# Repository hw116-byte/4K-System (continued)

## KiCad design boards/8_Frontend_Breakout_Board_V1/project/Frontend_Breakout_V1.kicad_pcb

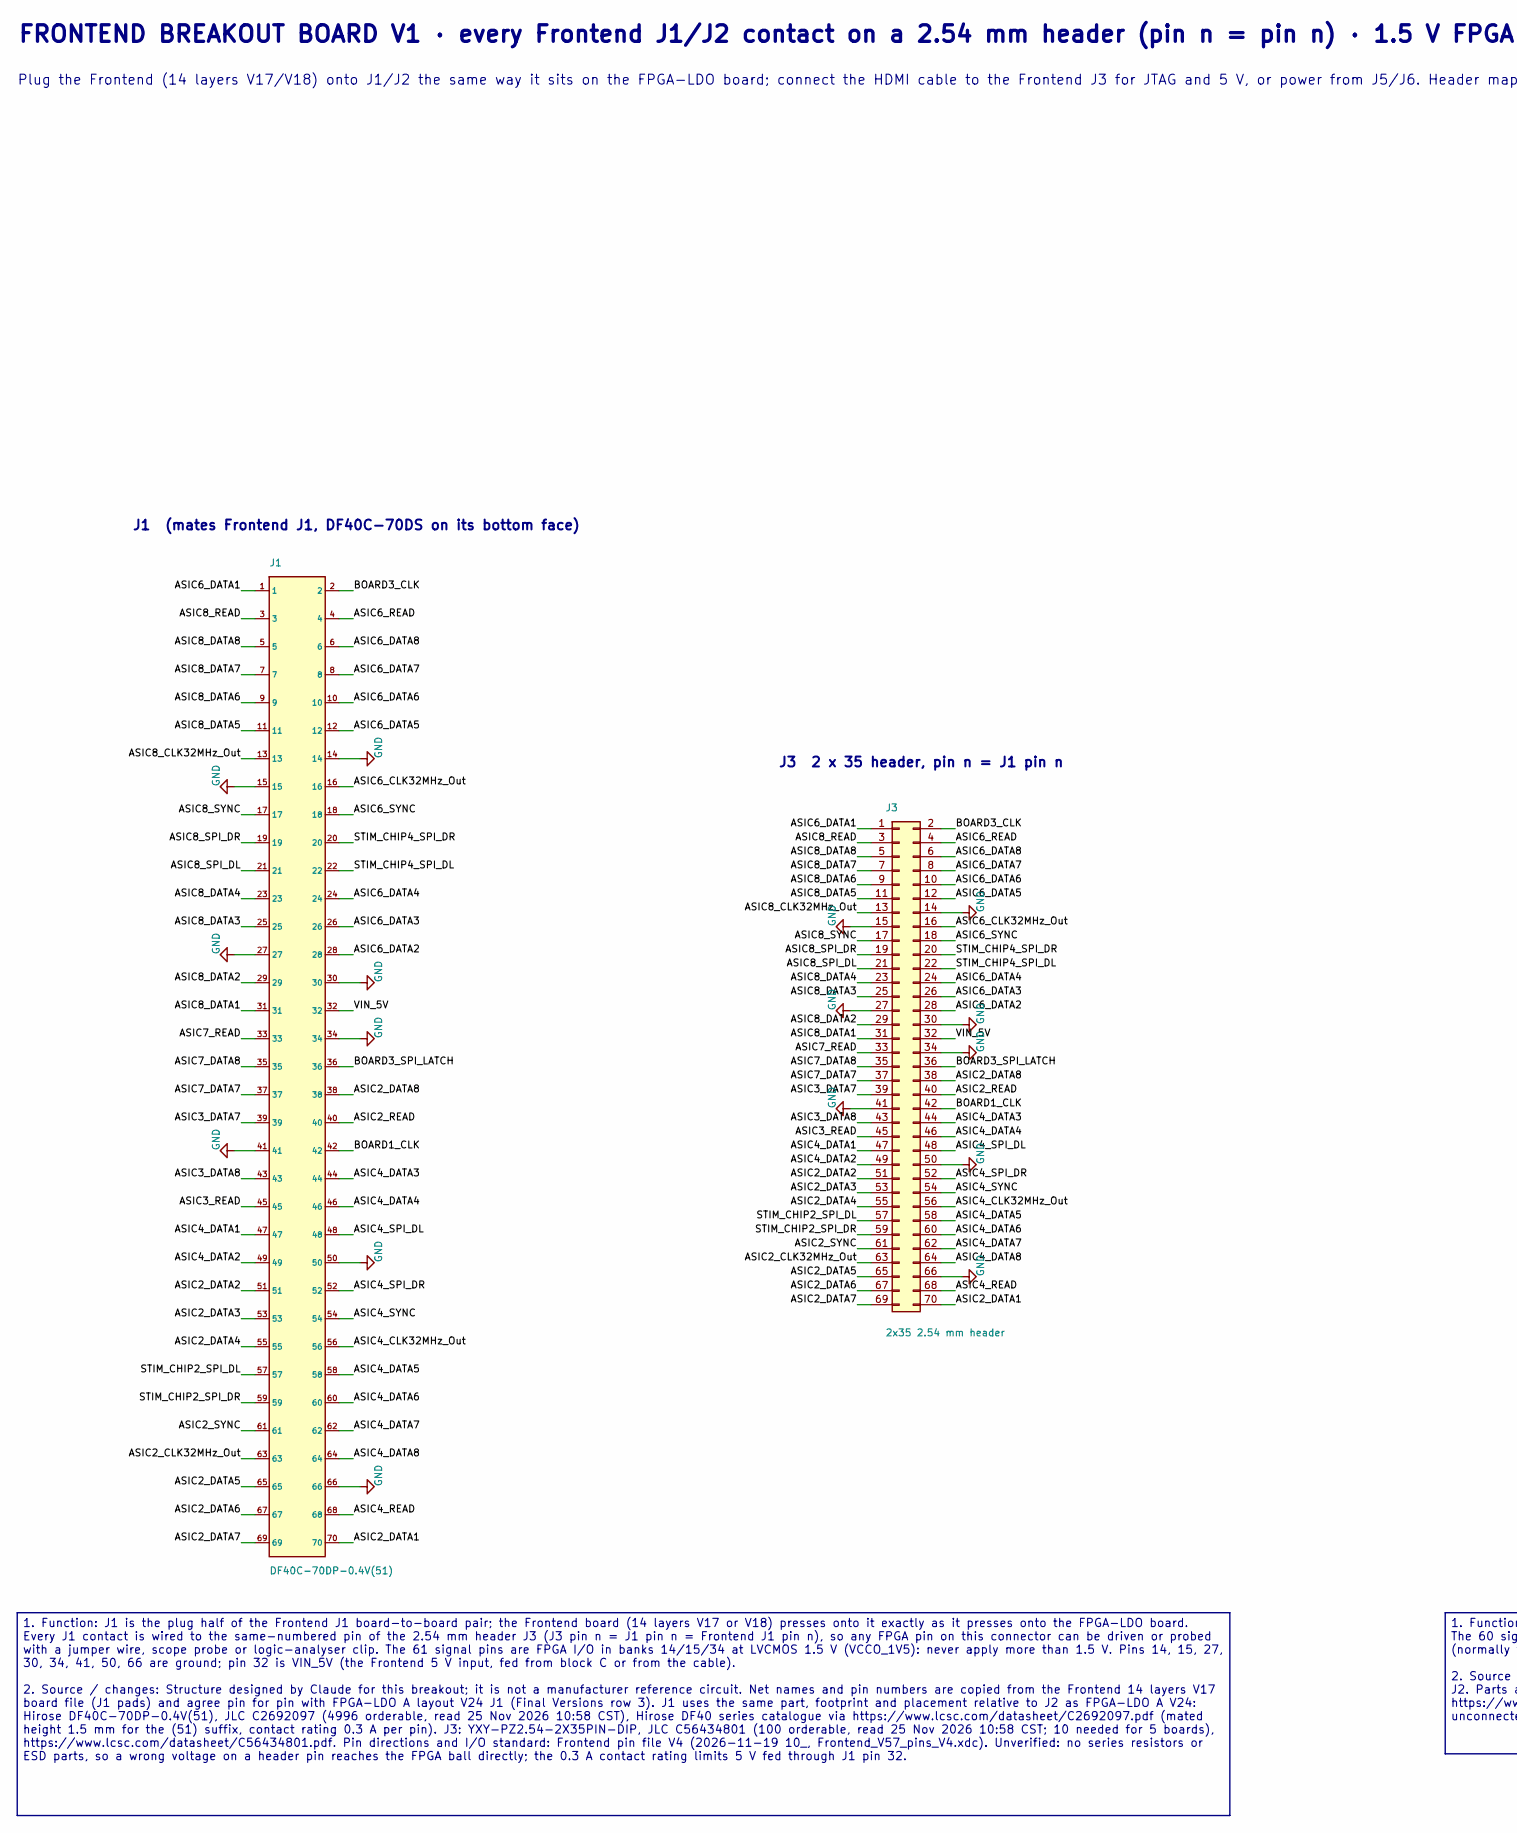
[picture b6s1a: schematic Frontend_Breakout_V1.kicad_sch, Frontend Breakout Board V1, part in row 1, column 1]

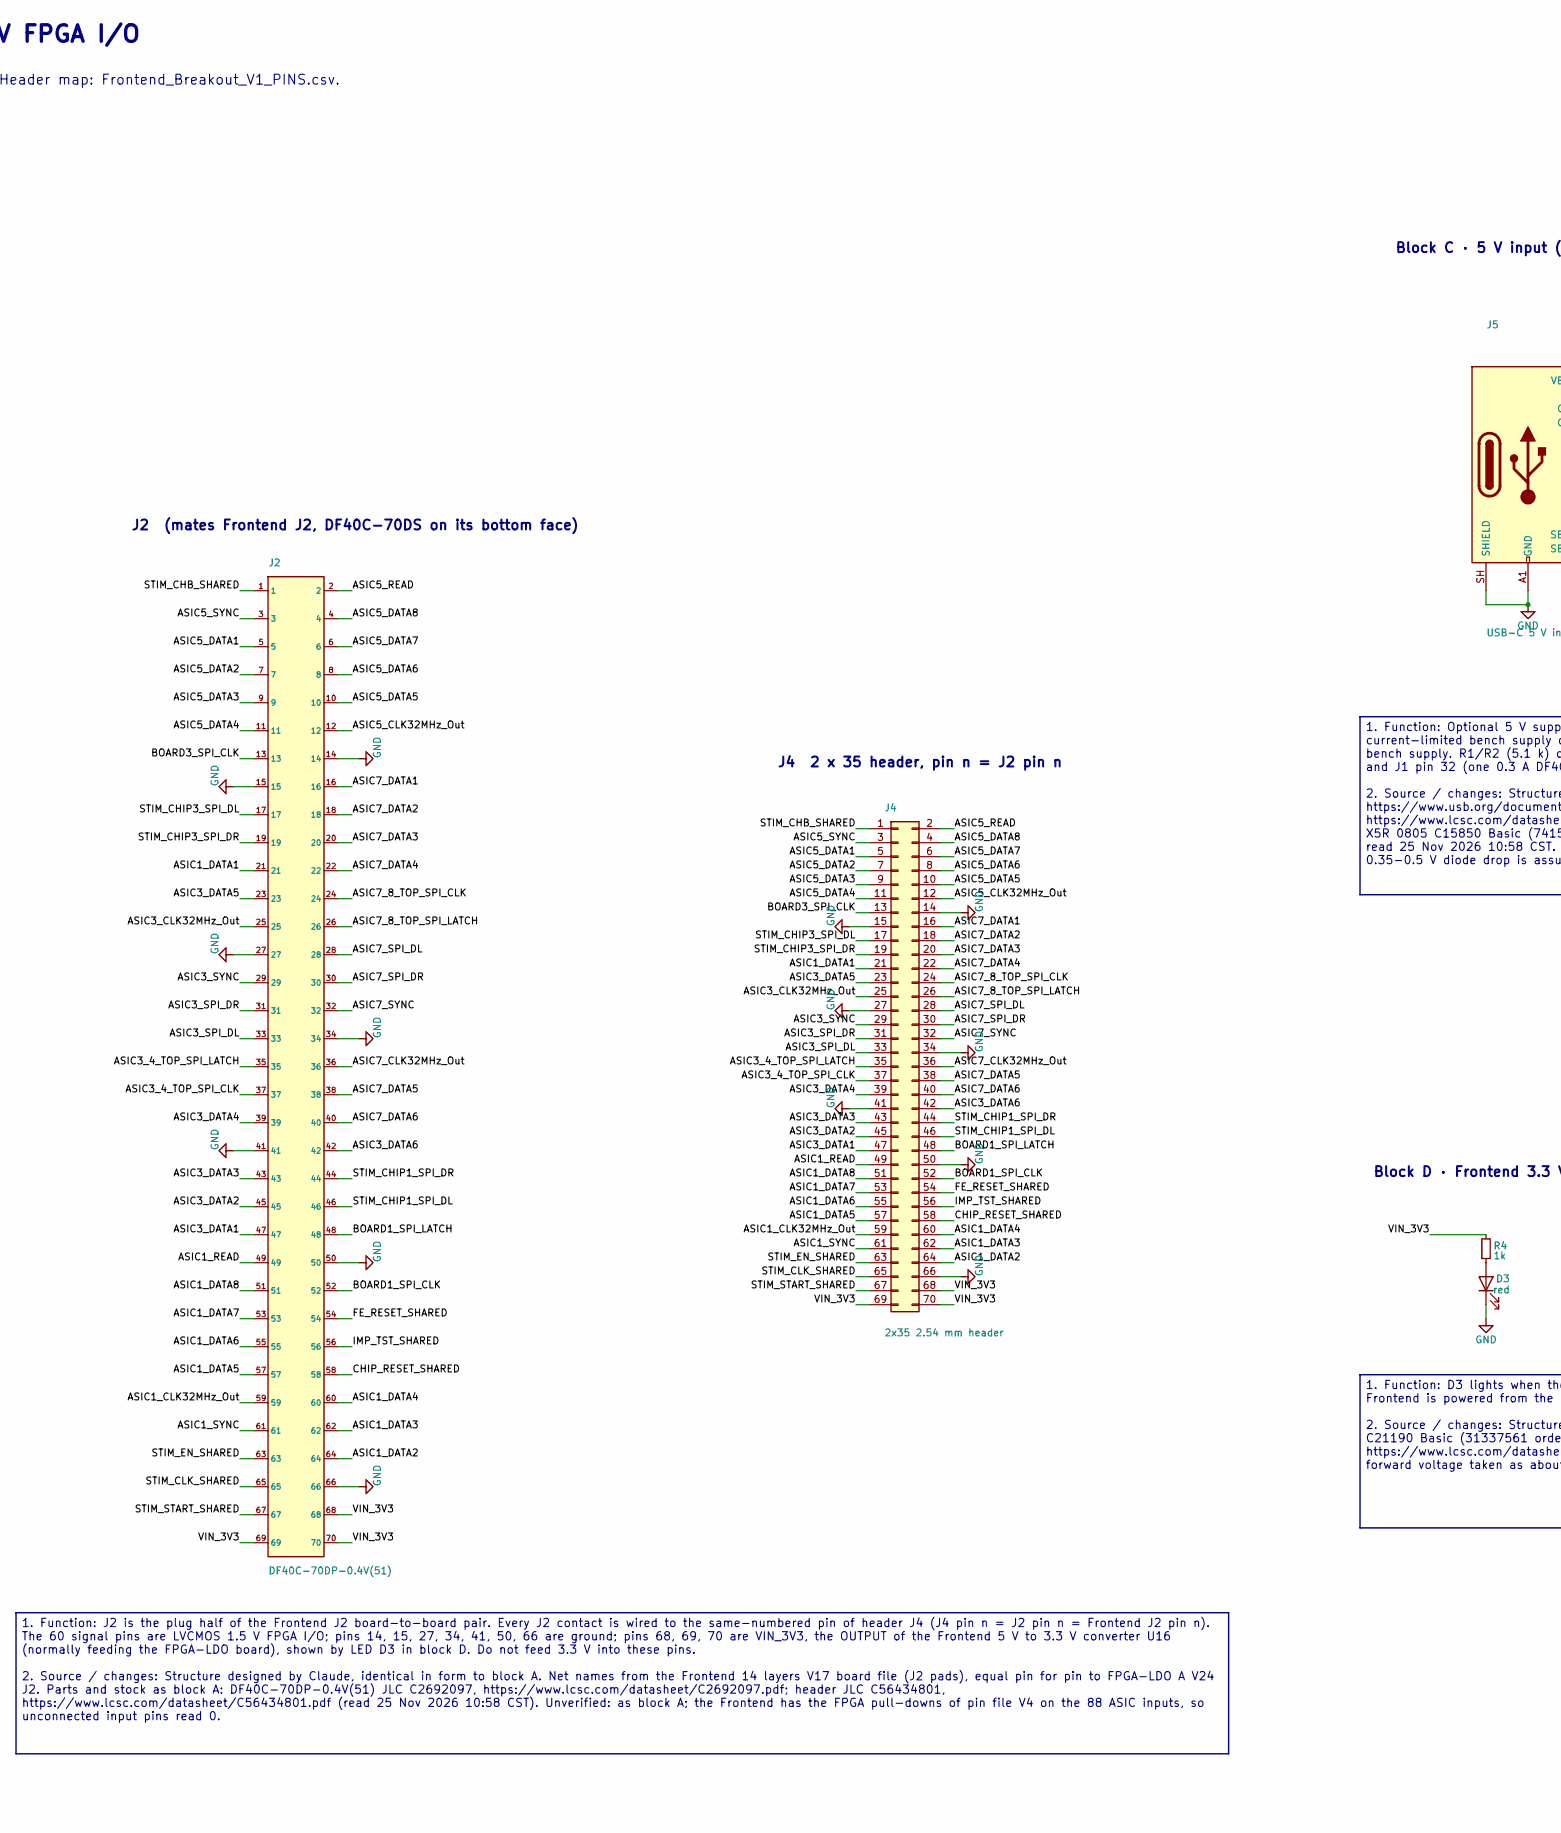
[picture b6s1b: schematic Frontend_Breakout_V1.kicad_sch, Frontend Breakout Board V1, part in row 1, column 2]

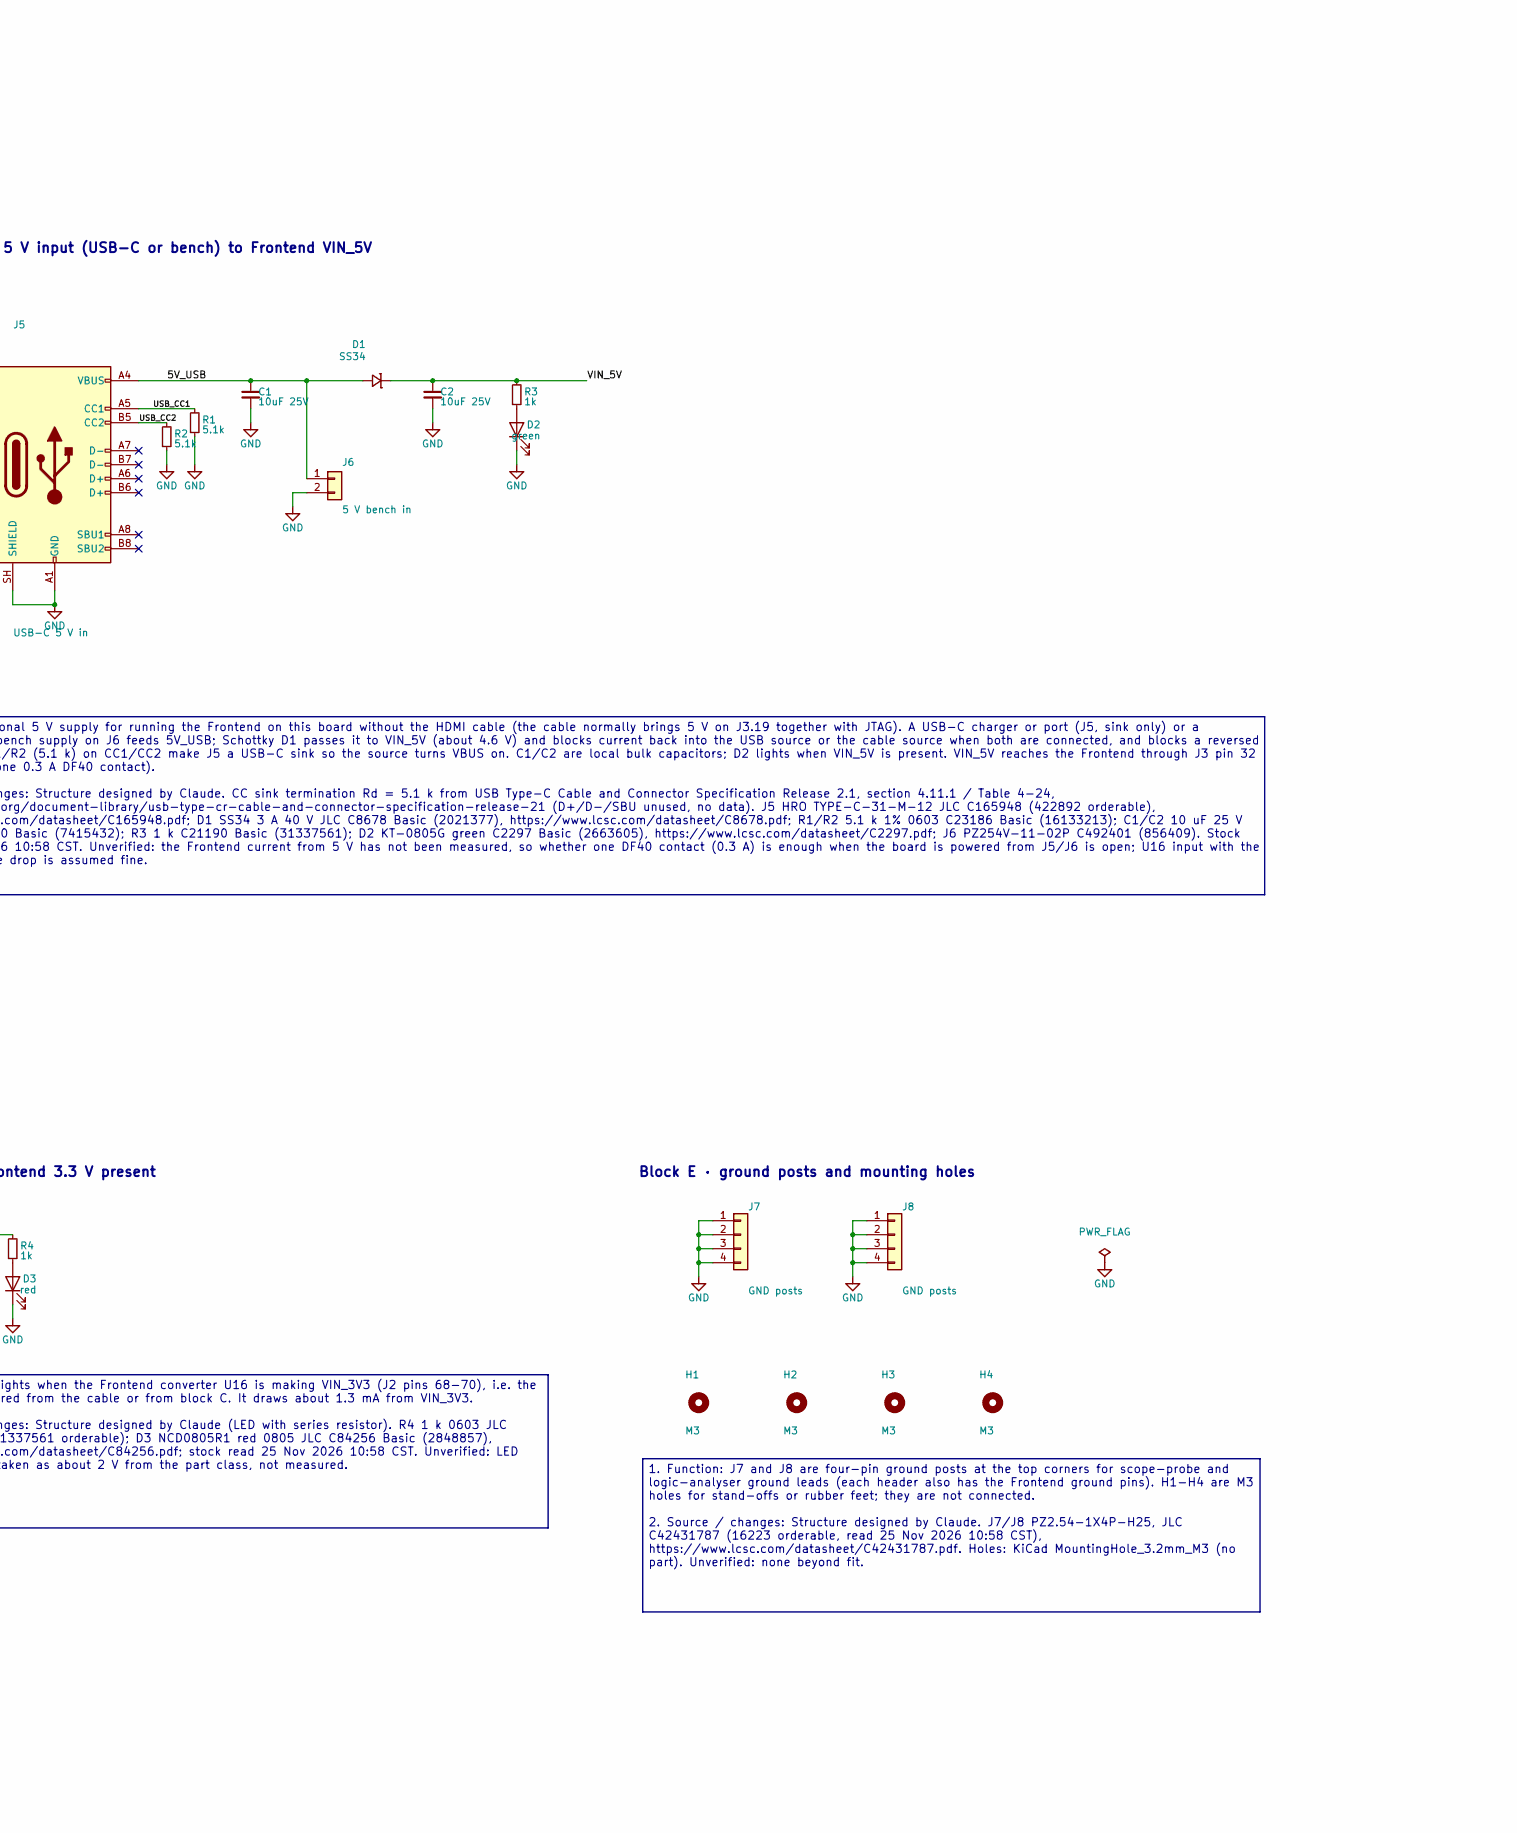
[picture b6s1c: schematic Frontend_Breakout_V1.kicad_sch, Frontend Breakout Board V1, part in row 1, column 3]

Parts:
C1, C2: 10uF 25V; C_0805_2012Metric; MPN CL21A106KAYNNNE; LCSC C15850
D1: SS34; D_SMA; MPN SS34; LCSC C8678
D2: green; LED_0805_2012Metric; MPN KT-0805G; LCSC C2297
D3: red; LED_0805_2012Metric; MPN NCD0805R1; LCSC C84256
H1, H2, H3, H4: M3; MountingHole_3.2mm_M3
J1, J2: DF40C-70DP-0.4V(51); Hirose_DF40C-70DP-0.4V_2x35-1MP_P0.4mm; MPN DF40C-70DP-0.4V(51); LCSC C2692097
J3, J4: 2x35 2.54 mm header; PinHeader_2x35_P2.54mm_Vertical; MPN YXY-PZ2.54-2X35PIN-DIP; LCSC C56434801
J5: USB-C 5 V in; USB_C_Receptacle_HRO_TYPE-C-31-M-12; MPN TYPE-C-31-M-12; LCSC C165948
J6: 5 V bench in; PinHeader_1x02_P2.54mm_Vertical; MPN PZ254V-11-02P; LCSC C492401
J7, J8: GND posts; PinHeader_1x04_P2.54mm_Vertical; MPN PZ2.54-1X4P-H25; LCSC C42431787
R1, R2: 5.1k; R_0603_1608Metric; MPN 0603WAF5101T5E; LCSC C23186
R3, R4: 1k; R_0603_1608Metric; MPN 0603WAF1001T5E; LCSC C21190

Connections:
/5V_USB: C1.1, D1.2 (A), J5.A4 (VBUS), J5.A9 (VBUS), J5.B4 (VBUS), J5.B9 (VBUS), J6.1
/ASIC1_CLK32MHz_Out: J2.59, J4.59
/ASIC1_DATA1: J2.21, J4.21
/ASIC1_DATA2: J2.64, J4.64
/ASIC1_DATA3: J2.62, J4.62
/ASIC1_DATA4: J2.60, J4.60
/ASIC1_DATA5: J2.57, J4.57
/ASIC1_DATA6: J2.55, J4.55
/ASIC1_DATA7: J2.53, J4.53
/ASIC1_DATA8: J2.51, J4.51
/ASIC1_READ: J2.49, J4.49
/ASIC1_SYNC: J2.61, J4.61
/ASIC2_CLK32MHz_Out: J1.63, J3.63
/ASIC2_DATA1: J1.70, J3.70
/ASIC2_DATA2: J1.51, J3.51
/ASIC2_DATA3: J1.53, J3.53
/ASIC2_DATA4: J1.55, J3.55
/ASIC2_DATA5: J1.65, J3.65
/ASIC2_DATA6: J1.67, J3.67
/ASIC2_DATA7: J1.69, J3.69
/ASIC2_DATA8: J1.38, J3.38
/ASIC2_READ: J1.40, J3.40
/ASIC2_SYNC: J1.61, J3.61
/ASIC3_4_TOP_SPI_CLK: J2.37, J4.37
/ASIC3_4_TOP_SPI_LATCH: J2.35, J4.35
/ASIC3_CLK32MHz_Out: J2.25, J4.25
/ASIC3_DATA1: J2.47, J4.47
/ASIC3_DATA2: J2.45, J4.45
/ASIC3_DATA3: J2.43, J4.43
/ASIC3_DATA4: J2.39, J4.39
/ASIC3_DATA5: J2.23, J4.23
/ASIC3_DATA6: J2.42, J4.42
/ASIC3_DATA7: J1.39, J3.39
/ASIC3_DATA8: J1.43, J3.43
/ASIC3_READ: J1.45, J3.45
/ASIC3_SPI_DL: J2.33, J4.33
/ASIC3_SPI_DR: J2.31, J4.31
/ASIC3_SYNC: J2.29, J4.29
/ASIC4_CLK32MHz_Out: J1.56, J3.56
/ASIC4_DATA1: J1.47, J3.47
/ASIC4_DATA2: J1.49, J3.49
/ASIC4_DATA3: J1.44, J3.44
/ASIC4_DATA4: J1.46, J3.46
/ASIC4_DATA5: J1.58, J3.58
/ASIC4_DATA6: J1.60, J3.60
/ASIC4_DATA7: J1.62, J3.62
/ASIC4_DATA8: J1.64, J3.64
/ASIC4_READ: J1.68, J3.68
/ASIC4_SPI_DL: J1.48, J3.48
/ASIC4_SPI_DR: J1.52, J3.52
/ASIC4_SYNC: J1.54, J3.54
/ASIC5_CLK32MHz_Out: J2.12, J4.12
/ASIC5_DATA1: J2.5, J4.5
/ASIC5_DATA2: J2.7, J4.7
/ASIC5_DATA3: J2.9, J4.9
/ASIC5_DATA4: J2.11, J4.11
/ASIC5_DATA5: J2.10, J4.10
/ASIC5_DATA6: J2.8, J4.8
/ASIC5_DATA7: J2.6, J4.6
/ASIC5_DATA8: J2.4, J4.4
/ASIC5_READ: J2.2, J4.2
/ASIC5_SYNC: J2.3, J4.3
/ASIC6_CLK32MHz_Out: J1.16, J3.16
/ASIC6_DATA1: J1.1, J3.1
/ASIC6_DATA2: J1.28, J3.28
/ASIC6_DATA3: J1.26, J3.26
/ASIC6_DATA4: J1.24, J3.24
/ASIC6_DATA5: J1.12, J3.12
/ASIC6_DATA6: J1.10, J3.10
/ASIC6_DATA7: J1.8, J3.8
/ASIC6_DATA8: J1.6, J3.6
/ASIC6_READ: J1.4, J3.4
/ASIC6_SYNC: J1.18, J3.18
/ASIC7_8_TOP_SPI_CLK: J2.24, J4.24
/ASIC7_8_TOP_SPI_LATCH: J2.26, J4.26
/ASIC7_CLK32MHz_Out: J2.36, J4.36
/ASIC7_DATA1: J2.16, J4.16
/ASIC7_DATA2: J2.18, J4.18
/ASIC7_DATA3: J2.20, J4.20
/ASIC7_DATA4: J2.22, J4.22
/ASIC7_DATA5: J2.38, J4.38
/ASIC7_DATA6: J2.40, J4.40
/ASIC7_DATA7: J1.37, J3.37
/ASIC7_DATA8: J1.35, J3.35
/ASIC7_READ: J1.33, J3.33
/ASIC7_SPI_DL: J2.28, J4.28
/ASIC7_SPI_DR: J2.30, J4.30
/ASIC7_SYNC: J2.32, J4.32
/ASIC8_CLK32MHz_Out: J1.13, J3.13
/ASIC8_DATA1: J1.31, J3.31
/ASIC8_DATA2: J1.29, J3.29
/ASIC8_DATA3: J1.25, J3.25
/ASIC8_DATA4: J1.23, J3.23
/ASIC8_DATA5: J1.11, J3.11
/ASIC8_DATA6: J1.9, J3.9
/ASIC8_DATA7: J1.7, J3.7
/ASIC8_DATA8: J1.5, J3.5
/ASIC8_READ: J1.3, J3.3
/ASIC8_SPI_DL: J1.21, J3.21
/ASIC8_SPI_DR: J1.19, J3.19
/ASIC8_SYNC: J1.17, J3.17
/BOARD1_CLK: J1.42, J3.42
/BOARD1_SPI_CLK: J2.52, J4.52
/BOARD1_SPI_LATCH: J2.48, J4.48
/BOARD3_CLK: J1.2, J3.2
/BOARD3_SPI_CLK: J2.13, J4.13
/BOARD3_SPI_LATCH: J1.36, J3.36
/CHIP_RESET_SHARED: J2.58, J4.58
/FE_RESET_SHARED: J2.54, J4.54
/IMP_TST_SHARED: J2.56, J4.56
/STIM_CHB_SHARED: J2.1, J4.1
/STIM_CHIP1_SPI_DL: J2.46, J4.46
/STIM_CHIP1_SPI_DR: J2.44, J4.44
/STIM_CHIP2_SPI_DL: J1.57, J3.57
/STIM_CHIP2_SPI_DR: J1.59, J3.59
/STIM_CHIP3_SPI_DL: J2.17, J4.17
/STIM_CHIP3_SPI_DR: J2.19, J4.19
/STIM_CHIP4_SPI_DL: J1.22, J3.22
/STIM_CHIP4_SPI_DR: J1.20, J3.20
/STIM_CLK_SHARED: J2.65, J4.65
/STIM_EN_SHARED: J2.63, J4.63
/STIM_START_SHARED: J2.67, J4.67
/USB_CC1: J5.A5 (CC1), R1.1
/USB_CC2: J5.B5 (CC2), R2.1
/VIN_3V3: J2.68, J2.69, J2.70, J4.68, J4.69, J4.70, R4.1
/VIN_5V: C2.1, D1.1 (K), J1.32, J3.32, R3.1
GND: C1.2, C2.2, D2.1 (K), D3.1 (K), J1.14, J1.15, J1.27, J1.30, J1.34, J1.41, J1.50, J1.66, J2.14, J2.15, J2.27, J2.34, J2.41, J2.50, J2.66, J3.14, J3.15, J3.27, J3.30, J3.34, J3.41, J3.50, J3.66, J4.14, J4.15, J4.27, J4.34, J4.41, J4.50, J4.66, J5.A1 (GND), J5.A12 (GND), J5.B1 (GND), J5.B12 (GND), J5.SH (SHIELD), J6.2, J7.1, J7.2, J7.3, J7.4, J8.1, J8.2, J8.3, J8.4, R1.2, R2.2
unnamed: D2.2 (A), R3.2
unnamed: D3.2 (A), R4.2

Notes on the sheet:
J1 (mates Frontend J1, DF40C-70DS on its bottom face)
J3 2 x 35 header, pin n = J1 pin n
J2 (mates Frontend J2, DF40C-70DS on its bottom face)
J4 2 x 35 header, pin n = J2 pin n
1. Function: J1 is the plug half of the Frontend J1 board-to-board pair; the Frontend board (14 layers V17 or V18) presses onto it exactly as it presses onto the FPGA-LDO board. Every J1 contact is wired to the same-numbered pin of the 2.54 mm header J3 (J3 pin n = J1 pin n = Frontend J1 pin n), so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
1. Function: J2 is the plug half of the Frontend J2 board-to-board pair. Every J2 contact is wired to the same-numbered pin of header J4 (J4 pin n = J2 pin n = Frontend J2 pin n). The 60 signal pins are LVCMOS 1.5 V FPGA I/O; pins 14, 15, 27, 34, 41, 50, 66 are ground; pins 68, 69, 70 are VIN_3V3, 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
Block C · 5 V input (USB-C or bench) to Frontend VIN_5V
1. Function: Optional 5 V supply for running the Frontend on this board without the HDMI cable (the cable normally brings 5 V on J3.19 together with JTAG). A USB-C charger or port (J5, sink only) or a current-limited bench supply on J6 feeds 5V_USB; Schottky D1 passes it to VIN_5V (about 4.6 V) and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
Block D · Frontend 3.3 V present
1. Function: D3 lights when the Frontend converter U16 is making VIN_3V3 (J2 pins 68-70), i.e. the Frontend is powered from the cable or from block C. It draws about 1.3 mA from VIN_3V3. 2. Source / changes: Structure designed by Claude (LED with series resistor). R4 1 k 0603 JLC C21190 Basic (3133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
Block E · ground posts and mounting holes
1. Function: J7 and J8 are four-pin ground posts at the top corners for scope-probe and logic-analyser ground leads (each header also has the Frontend ground pins). H1-H4 are M3 holes for stand-offs or rubber feet; they are not connected. 2. Source / changes: Structure designed by Claude. J7/J8 PZ2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
FRONTEND BREAKOUT BOARD V1 · every Frontend J1/J2 contact on a 2.54 mm header (pin n = pin n) · 1.5 V FPGA I/O
Plug the Frontend (14 layers V17/V18) onto J1/J2 the same way it sits on the FPGA-LDO board; connect the HDMI cable to the Frontend J3 for JTAG and 5 V, or power from J5/J6. Header map: Frontend_Breakout_V1_PINS.csv.

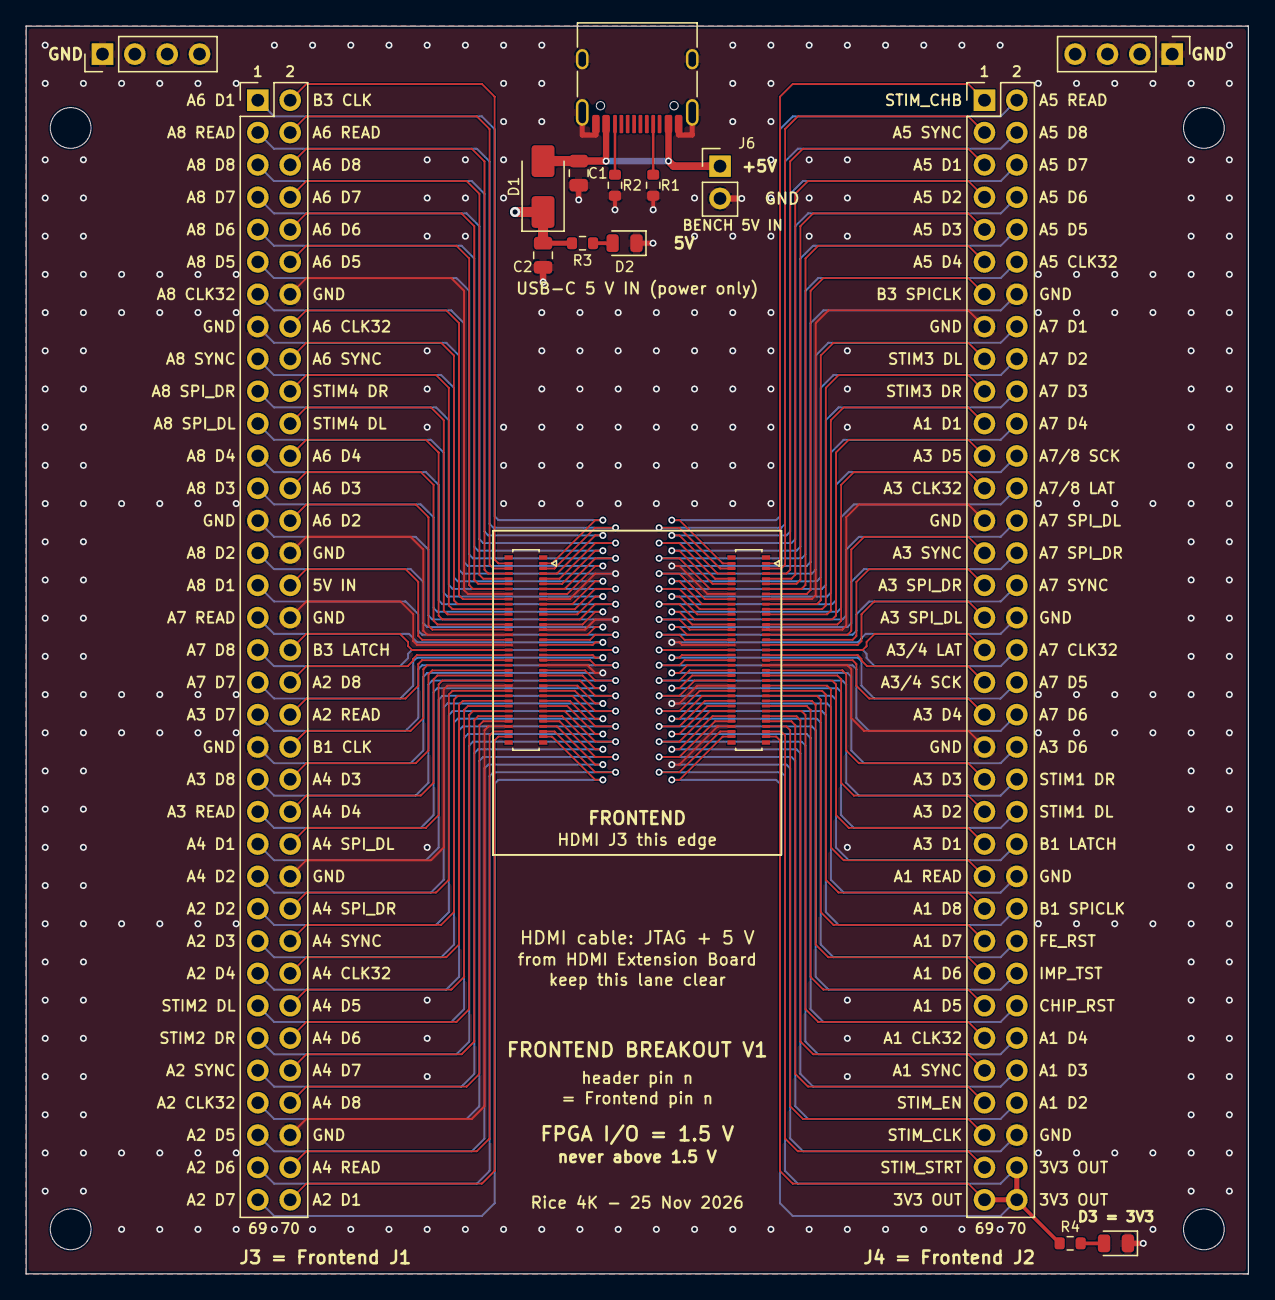
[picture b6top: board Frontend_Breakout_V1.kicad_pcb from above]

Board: 4 copper layers, 96.0 x 98.0 mm, 21 parts (0 on the bottom side), 129 nets.

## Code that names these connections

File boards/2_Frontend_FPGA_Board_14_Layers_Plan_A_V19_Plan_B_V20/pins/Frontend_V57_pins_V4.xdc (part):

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
# ---- 2. The 88 inputs from the ASICs (8 data, READ, SYNC and the returned 32 MHz clock per chip).
# PULLDOWN: the chip pads have no pull resistors (meeting of 12 Nov 2026, answer C2) and a missing or unpowered ASIC board would leave the inputs floating (SYS-77).
set_property -dict {PACKAGE_PIN R2 IOSTANDARD LVCMOS15 PULLDOWN true} [get_ports {ASIC1_CLK32MHz_Out}]   ;# J2.59 IO_L13P_T2_MRCC_34, ASIC port J4.45
set_property -dict {PACKAGE_PIN U2 IOSTANDARD LVCMOS15 PULLDOWN true} [get_ports {ASIC1_DATA1}]   ;# J2.21 IO_L15P_T2_DQS_34, ASIC port J4.79
set_property -dict {PACKAGE_PIN J4 IOSTANDARD LVCMOS15 PULLDOWN true} [get_ports {ASIC1_DATA2}]   ;# J2.64 IO_L2N_T0_34, ASIC port J4.77
set_property -dict {PACKAGE_PIN K2 IOSTANDARD LVCMOS15 PULLDOWN true} [get_ports {ASIC1_DATA3}]   ;# J2.62 IO_L3P_T0_DQS_34, ASIC port J4.75
set_property -dict {PACKAGE_PIN K1 IOSTANDARD LVCMOS15 PULLDOWN true} [get_ports {ASIC1_DATA4}]   ;# J2.60 IO_L3N_T0_DQS_34, ASIC port J4.73
set_property -dict {PACKAGE_PIN M1 IOSTANDARD LVCMOS15 PULLDOWN true} [get_ports {ASIC1_DATA5}]   ;# J2.57 IO_L7N_T1_34, ASIC port J4.43
set_property -dict {PACKAGE_PIN N1 IOSTANDARD LVCMOS15 PULLDOWN true} [get_ports {ASIC1_DATA6}]   ;# J2.55 IO_L9P_T1_DQS_34, ASIC port J4.41
set_property -dict {PACKAGE_PIN P1 IOSTANDARD LVCMOS15 PULLDOWN true} [get_ports {ASIC1_DATA7}]   ;# J2.53 IO_L9N_T1_DQS_34, ASIC port J4.39
set_property -dict {PACKAGE_PIN L3 IOSTANDARD LVCMOS15 PULLDOWN true} [get_ports {ASIC1_DATA8}]   ;# J2.51 IO_L5N_T0_34, ASIC port J4.37
set_property -dict {PACKAGE_PIN L2 IOSTANDARD LVCMOS15 PULLDOWN true} [get_ports {ASIC1_READ}]   ;# J2.49 IO_L4N_T0_34, ASIC port J4.35
set_property -dict {PACKAGE_PIN J5 IOSTANDARD LVCMOS15 PULLDOWN true} [get_ports {ASIC1_SYNC}]   ;# J2.61 IO_L2P_T0_34, ASIC port J4.47
set_property -dict {PACKAGE_PIN D13 IOSTANDARD LVCMOS15 PULLDOWN true} [get_ports {ASIC2_CLK32MHz_Out}]   ;# J1.63 IO_L11P_T1_SRCC_15, ASIC port J4.19
set_property -dict {PACKAGE_PIN A17 IOSTANDARD LVCMOS15 PULLDOWN true} [get_ports {ASIC2_DATA1}]   ;# J1.70 IO_L15N_T2_DQS_ADV_B_15, ASIC port J4.33
set_property -dict {PACKAGE_PIN E15 IOSTANDARD LVCMOS15 PULLDOWN true} [get_ports {ASIC2_DATA2}]   ;# J1.51 IO_L13P_T2_MRCC_15, ASIC port J4.31
set_property -dict {PACKAGE_PIN D16 IOSTANDARD LVCMOS15 PULLDOWN true} [get_ports {ASIC2_DATA3}]   ;# J1.53 IO_L14N_T2_SRCC_15, ASIC port J4.29
set_property -dict {PACKAGE_PIN D15 IOSTANDARD LVCMOS15 PULLDOWN true} [get_ports {ASIC2_DATA4}]   ;# J1.55 IO_L13N_T2_MRCC_15, ASIC port J4.27
set_property -dict {PACKAGE_PIN B14 IOSTANDARD LVCMOS15 PULLDOWN true} [get_ports {ASIC2_DATA5}]   ;# J1.65 IO_L10P_T1_AD11P_15, ASIC port J4.17
set_property -dict {PACKAGE_PIN A15 IOSTANDARD LVCMOS15 PULLDOWN true} [get_ports {ASIC2_DATA6}]   ;# J1.67 IO_L10N_T1_AD11N_15, ASIC port J4.15
set_property -dict {PACKAGE_PIN A14 IOSTANDARD LVCMOS15 PULLDOWN true} [get_ports {ASIC2_DATA7}]   ;# J1.69 IO_L8N_T1_AD10N_15, ASIC port J4.13
set_property -dict {PACKAGE_PIN H17 IOSTANDARD LVCMOS15 PULLDOWN true} [get_ports {ASIC2_DATA8}]   ;# J1.38 IO_L23P_T3_FOE_B_15, ASIC port J4.11
set_property -dict {PACKAGE_PIN H18 IOSTANDARD LVCMOS15 PULLDOWN true} [get_ports {ASIC2_READ}]   ;# J1.40 IO_L23N_T3_FWE_B_15, ASIC port J4.9
set_property -dict {PACKAGE_PIN B15 IOSTANDARD LVCMOS15 PULLDOWN true} [get_ports {ASIC2_SYNC}]   ;# J1.61 IO_L9N_T1_DQS_AD3N_15, ASIC port J4.21
set_property -dict {PACKAGE_PIN P4 IOSTANDARD LVCMOS15 PULLDOWN true} [get_ports {ASIC3_CLK32MHz_Out}]   ;# J2.25 IO_L12P_T1_MRCC_34, ASIC port J4.62, lane swap on the Frontend: this contact was on ball R7
set_property -dict {PACKAGE_PIN L5 IOSTANDARD LVCMOS15 PULLDOWN true} [get_ports {ASIC3_DATA1}]   ;# J2.47 IO_L6P_T0_34, ASIC port J4.80
set_property -dict {PACKAGE_PIN M6 IOSTANDARD LVCMOS15 PULLDOWN true} [get_ports {ASIC3_DATA2}]   ;# J2.45 IO_L8P_T1_34, ASIC port J4.78
set_property -dict {PACKAGE_PIN N2 IOSTANDARD LVCMOS15 PULLDOWN true} [get_ports {ASIC3_DATA3}]   ;# J2.43 IO_L11N_T1_SRCC_34, ASIC port J4.76
set_property -dict {PACKAGE_PIN N6 IOSTANDARD LVCMOS15 PULLDOWN true} [get_ports {ASIC3_DATA4}]   ;# J2.39 IO_L8N_T1_34, ASIC port J4.74
set_property -dict {PACKAGE_PIN T2 IOSTANDARD LVCMOS15 PULLDOWN true} [get_ports {ASIC3_DATA5}]   ;# J2.23 IO_L14N_T2_SRCC_34, ASIC port J4.60, V5 name on this wire: ASIC3_READ
set_property -dict {PACKAGE_PIN D9 IOSTANDARD LVCMOS15 PULLDOWN true} [get_ports {ASIC3_DATA6}]   ;# J2.42 IO_L2P_T0_AD8P_15, ASIC port J4.58, new wire
set_property -dict {PACKAGE_PIN D14 IOSTANDARD LVCMOS15 PULLDOWN true} [get_ports {ASIC3_DATA7}]   ;# J1.39 IO_L12N_T1_MRCC_15, ASIC port J4.32, new wire
set_property -dict {PACKAGE_PIN G15 IOSTANDARD LVCMOS15 PULLDOWN true} [get_ports {ASIC3_DATA8}]   ;# J1.43 IO_L21P_T3_DQS_15, ASIC port J4.30, new wire
set_property -dict {PACKAGE_PIN F14 IOSTANDARD LVCMOS15 PULLDOWN true} [get_ports {ASIC3_READ}]   ;# J1.45 IO_L22N_T3_A16_15, ASIC port J4.28, new wire
set_property -dict {PACKAGE_PIN T3 IOSTANDARD LVCMOS15 PULLDOWN true} [get_ports {ASIC3_SYNC}]   ;# J2.29 IO_L17N_T2_34, ASIC port J4.64, V5 name on this wire: ASIC3_DATA7
set_property -dict {PACKAGE_PIN E16 IOSTANDARD LVCMOS15 PULLDOWN true} [get_ports {ASIC4_CLK32MHz_Out}]   ;# J1.56 IO_L14P_T2_SRCC_15, ASIC port J4.12
set_property -dict {PACKAGE_PIN F15 IOSTANDARD LVCMOS15 PULLDOWN true} [get_ports {ASIC4_DATA1}]   ;# J1.47 IO_L21N_T3_DQS_A18_15, ASIC port J4.26, new wire
set_property -dict {PACKAGE_PIN E13 IOSTANDARD LVCMOS15 PULLDOWN true} [get_ports {ASIC4_DATA2}]   ;# J1.49 IO_L12P_T1_MRCC_15, ASIC port J4.24, new wire
set_property -dict {PACKAGE_PIN G17 IOSTANDARD LVCMOS15 PULLDOWN true} [get_ports {ASIC4_DATA3}]   ;# J1.44 IO_L19P_T3_A22_15, ASIC port J4.22, V5 name on this wire: ASIC4_DATA1
set_property -dict {PACKAGE_PIN F17 IOSTANDARD LVCMOS15 PULLDOWN true} [get_ports {ASIC4_DATA4}]   ;# J1.46 IO_L24P_T3_RS1_15, ASIC port J4.20, V5 name on this wire: ASIC4_DATA2
set_property -dict {PACKAGE_PIN D18 IOSTANDARD LVCMOS15 PULLDOWN true} [get_ports {ASIC4_DATA5}]   ;# J1.58 IO_L17N_T2_A25_15, ASIC port J4.10
set_property -dict {PACKAGE_PIN C18 IOSTANDARD LVCMOS15 PULLDOWN true} [get_ports {ASIC4_DATA6}]   ;# J1.60 IO_L18N_T2_A23_15, ASIC port J4.8
set_property -dict {PACKAGE_PIN C17 IOSTANDARD LVCMOS15 PULLDOWN true} [get_ports {ASIC4_DATA7}]   ;# J1.62 IO_L18P_T2_A24_15, ASIC port J4.6
set_property -dict {PACKAGE_PIN B17 IOSTANDARD LVCMOS15 PULLDOWN true} [get_ports {ASIC4_DATA8}]   ;# J1.64 IO_L16N_T2_A27_15, ASIC port J4.4
set_property -dict {PACKAGE_PIN B16 IOSTANDARD LVCMOS15 PULLDOWN true} [get_ports {ASIC4_READ}]   ;# J1.68 IO_L15P_T2_DQS_15, ASIC port J4.2
set_property -dict {PACKAGE_PIN E17 IOSTANDARD LVCMOS15 PULLDOWN true} [get_ports {ASIC4_SYNC}]   ;# J1.54 IO_L17P_T2_A26_15, ASIC port J4.14
set_property -dict {PACKAGE_PIN R3 IOSTANDARD LVCMOS15 PULLDOWN true} [get_ports {ASIC5_CLK32MHz_Out}]   ;# J2.12 IO_L14P_T2_SRCC_34, ASIC port J3.45
set_property -dict {PACKAGE_PIN V4 IOSTANDARD LVCMOS15 PULLDOWN true} [get_ports {ASIC5_DATA1}]   ;# J2.5 IO_L18N_T2_34, ASIC port J3.79
set_property -dict {PACKAGE_PIN U1 IOSTANDARD LVCMOS15 PULLDOWN true} [get_ports {ASIC5_DATA2}]   ;# J2.7 IO_L15N_T2_DQS_34, ASIC port J3.77
set_property -dict {PACKAGE_PIN U4 IOSTANDARD LVCMOS15 PULLDOWN true} [get_ports {ASIC5_DATA3}]   ;# J2.9 IO_L18P_T2_34, ASIC port J3.75
set_property -dict {PACKAGE_PIN U5 IOSTANDARD LVCMOS15 PULLDOWN true} [get_ports {ASIC5_DATA4}]   ;# J2.11 IO_L20N_T3_34, ASIC port J3.73
set_property -dict {PACKAGE_PIN T5 IOSTANDARD LVCMOS15 PULLDOWN true} [get_ports {ASIC5_DATA5}]   ;# J2.10 IO_L21N_T3_DQS_34, ASIC port J3.43
set_property -dict {PACKAGE_PIN T4 IOSTANDARD LVCMOS15 PULLDOWN true} [get_ports {ASIC5_DATA6}]   ;# J2.8 IO_L17P_T2_34, ASIC port J3.41
set_property -dict {PACKAGE_PIN U6 IOSTANDARD LVCMOS15 PULLDOWN true} [get_ports {ASIC5_DATA7}]   ;# J2.6 IO_L20P_T3_34, ASIC port J3.39
set_property -dict {PACKAGE_PIN U7 IOSTANDARD LVCMOS15 PULLDOWN true} [get_ports {ASIC5_DATA8}]   ;# J2.4 IO_L23P_T3_34, ASIC port J3.37
set_property -dict {PACKAGE_PIN V3 IOSTANDARD LVCMOS15 PULLDOWN true} [get_ports {ASIC5_READ}]   ;# J2.2 IO_L16P_T2_34, ASIC port J3.35
set_property -dict {PACKAGE_PIN V2 IOSTANDARD LVCMOS15 PULLDOWN true} [get_ports {ASIC5_SYNC}]   ;# J2.3 IO_L16N_T2_34, ASIC port J3.47
set_property -dict {PACKAGE_PIN R16 IOSTANDARD LVCMOS15 PULLDOWN true} [get_ports {ASIC6_CLK32MHz_Out}]   ;# J1.16 IO_L14P_T2_SRCC_14, ASIC port J3.19
set_property -dict {PACKAGE_PIN V16 IOSTANDARD LVCMOS15 PULLDOWN true} [get_ports {ASIC6_DATA1}]   ;# J1.1 IO_L18P_T2_A12_D28_14, ASIC port J3.33
set_property -dict {PACKAGE_PIN K18 IOSTANDARD LVCMOS15 PULLDOWN true} [get_ports {ASIC6_DATA2}]   ;# J1.28 IO_L3N_T0_DQS_EMCCLK_14, ASIC port J3.31
set_property -dict {PACKAGE_PIN L18 IOSTANDARD LVCMOS15 PULLDOWN true} [get_ports {ASIC6_DATA3}]   ;# J1.26 IO_L4N_T0_D05_14, ASIC port J3.29
set_property -dict {PACKAGE_PIN M17 IOSTANDARD LVCMOS15 PULLDOWN true} [get_ports {ASIC6_DATA4}]   ;# J1.24 IO_L7N_T1_D10_14, ASIC port J3.27
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
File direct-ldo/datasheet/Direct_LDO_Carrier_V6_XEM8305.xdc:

# Direct LDO Carrier V6 -> Opal Kelly XEM8305 (XCAU15P-2FFVB676E), Bank 64 at 1.5 V
# Made 23 Nov 2026 from the V6 netlist (J1/MC1, board edited 31 Oct 2026, 20:17 CST) and the Opal Kelly XEM8305 pin list
# (https://pins.opalkelly.com/pin_list/XEM8305). All 23 balls cross-checked.
# Do NOT use the older xem8305_asic_bank64_candidate.xdc (5 Oct 2026): 22 of its 23 balls are wrong for V6.
# Bank 64 VCCO is 1.5 V, made on the carrier by U2 (enabled by XEM8305_PG), so every pin is LVCMOS15.
# Outputs start at low drive and slow slew: the carrier lines are about 55 mm long and unterminated.
# Add the FrontPanel host-interface pins separately (Opal Kelly sample XDC or the Pins site generator).

# ---- ASIC -> FPGA (inputs) ----
set_property -dict {PACKAGE_PIN AF22 IOSTANDARD LVCMOS15} [get_ports asic_d1]   ;# D1, J1.4, MC1.85
set_property -dict {PACKAGE_PIN AE22 IOSTANDARD LVCMOS15} [get_ports asic_d2]   ;# D2, J1.6, MC1.83
set_property -dict {PACKAGE_PIN AE23 IOSTANDARD LVCMOS15} [get_ports asic_d3]   ;# D3, J1.8, MC1.81
set_property -dict {PACKAGE_PIN AD23 IOSTANDARD LVCMOS15} [get_ports asic_d4]   ;# D4, J1.10, MC1.79
set_property -dict {PACKAGE_PIN AA19 IOSTANDARD LVCMOS15} [get_ports asic_sync]   ;# SYNC, J1.34, MC1.51
set_property -dict {PACKAGE_PIN AD21 IOSTANDARD LVCMOS15} [get_ports asic_clk32mhz]   ;# CLK32MHZ, J1.36, MC1.67
set_property -dict {PACKAGE_PIN AA20 IOSTANDARD LVCMOS15} [get_ports asic_d5]   ;# D5, J1.38, MC1.47
set_property -dict {PACKAGE_PIN AC17 IOSTANDARD LVCMOS15} [get_ports asic_d6]   ;# D6, J1.40, MC1.45
set_property -dict {PACKAGE_PIN AB17 IOSTANDARD LVCMOS15} [get_ports asic_d7]   ;# D7, J1.42, MC1.43
set_property -dict {PACKAGE_PIN AA17 IOSTANDARD LVCMOS15} [get_ports asic_d8]   ;# D8, J1.44, MC1.41
set_property -dict {PACKAGE_PIN Y17  IOSTANDARD LVCMOS15} [get_ports asic_read]   ;# READ, J1.46, MC1.39

# ---- FPGA -> ASIC (outputs) ----
set_property -dict {PACKAGE_PIN AC23 IOSTANDARD LVCMOS15 DRIVE 4 SLEW SLOW} [get_ports asic_clkh]   ;# CLKH, J1.12, MC1.77
set_property -dict {PACKAGE_PIN AC22 IOSTANDARD LVCMOS15 DRIVE 4 SLEW SLOW} [get_ports asic_chip_reset]   ;# CHIP_RESET, J1.14, MC1.75
set_property -dict {PACKAGE_PIN AA22 IOSTANDARD LVCMOS15 DRIVE 4 SLEW SLOW} [get_ports asic_imp_test]   ;# IMP_TEST, J1.18, MC1.71
set_property -dict {PACKAGE_PIN AE21 IOSTANDARD LVCMOS15 DRIVE 4 SLEW SLOW} [get_ports asic_fe_reset]   ;# FE_RESET, J1.20, MC1.69
set_property -dict {PACKAGE_PIN AB20 IOSTANDARD LVCMOS15 DRIVE 4 SLEW SLOW} [get_ports asic_spi_clk]   ;# SPI_CLK, J1.22, MC1.49
set_property -dict {PACKAGE_PIN AC21 IOSTANDARD LVCMOS15 DRIVE 4 SLEW SLOW} [get_ports asic_spi_latch]   ;# SPI_LATCH, J1.24, MC1.65
set_property -dict {PACKAGE_PIN AB21 IOSTANDARD LVCMOS15 DRIVE 4 SLEW SLOW} [get_ports asic_spi_dinl]   ;# SPI_DINL, J1.26, MC1.63
set_property -dict {PACKAGE_PIN AB22 IOSTANDARD LVCMOS15 DRIVE 4 SLEW SLOW} [get_ports asic_stim_start]   ;# STIM_START, J1.27, MC1.73
set_property -dict {PACKAGE_PIN Y21  IOSTANDARD LVCMOS15 DRIVE 4 SLEW SLOW} [get_ports asic_spi_dinr]   ;# SPI_DINR, J1.28, MC1.57
set_property -dict {PACKAGE_PIN Y20  IOSTANDARD LVCMOS15 DRIVE 4 SLEW SLOW} [get_ports asic_stim_clk]   ;# STIM_CLK, J1.29, MC1.55
set_property -dict {PACKAGE_PIN AB19 IOSTANDARD LVCMOS15 DRIVE 4 SLEW SLOW} [get_ports asic_stim_en]   ;# STIM_EN, J1.31, MC1.53
set_property -dict {PACKAGE_PIN AA18 IOSTANDARD LVCMOS15 DRIVE 4 SLEW SLOW} [get_ports asic_stim_chb]   ;# STIM_CHB, J1.33, MC1.37

# Returned ASIC clock. 31.25 ns = 32 MHz. If CLKH is run at 16 MHz (as the 2026 bench firmware did), use 62.5.
create_clock -period 31.250 -name asic_clk32 [get_ports asic_clk32mhz]
# Input delays of D1-D8/READ/SYNC relative to asic_clk32 are not specified by any source yet; measure, then add
# set_input_delay constraints. Capture on the falling edge of asic_clk32 (see the datasheet, section 8).
